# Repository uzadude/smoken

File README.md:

# Smoken!
A temperature controlled fan for charcoal smoker using ESP32.
 
## Background
After taking a welding course, I decided to build a smoker. Shortly after, I realized I must have a solution to keep the temperature steady for many hours. Searching around the internet I found only terribly expensive products (like the [FIREBOARD](https://www.fireboard.com/shop/fireboard-2-drive/?fba_ref=14)). That motivated me to try my first IOT project!

I took this opportunity to gain some skills in the electrical engineering domain.
I used an ESP32 for the MCU (started from [ESP32 starter kit](https://www.ebay.com/itm/303652581313)), built a working prototype using a breadboard and then went on to design a PCB for it (using [KiCad](https://www.kicad.org/)).

I will try to highlight the main lessons learned throughout this process.

## How It Works
- An ESP32 is connected to a thermocouple (with max6675 amplifier) to measure the smoker's current temprature. Another thermocouple is connected just to monitor the meat's temprature.
- The ESP32 is also connected to a 4-pin fan and controls it through a PWM channel with A PID algorithm.
- An external power of 12V/5A is used for both the fan and the ESP32 (through a step-down regulator).
- An 1602 LCD screen is used for simple information.
- A web server is used to monitor the current status, and configure things like the wifi credentials and some paramteres.
- A potentiometer is also available to have manual control over the fan.

### Circuit Schema

### Inventory List

|name|price|quantity|
|----|----|---|
|Esp 32|4|1
|12v power supply|3.7|1
|12v/3A blower fan 4pin|15.4|1
|12v to 5v step down|4|4
|LCD 1602|2.4|1
|max6675|7.3|2
|thermocouple|5.3|2
|small bread board|4.3|3
|4p connector|2.6|10
|wire 4p|5|5m
|3.3k resistor|1.5|300
|wires|3|120

### Afterthoughts
- I could have used a much weaker fan
- Replace the 1602 LCD with 12864 OLED

### Gotchas
- Fan's tacho required RC filter to get the correct reading
- Pin 4 as ADC with wifi.h [bug](https://github.com/espressif/arduino-esp32/issues/102)

## Code
- Use Platform IO as it is way more convenient than the Arduino IDE
- Web server using ESPAsyncWebServer
- Web-based config using AsyncWebConfig
- Use the SPIFFS to save data like a webpage, config file, and data history
- Use git from the beginning

### Gotchas
- [PWM's max freq/precision](src/fan.cpp#L18)

### Some Refs
- basic ESP32 examples:
  - https://lastminuteengineers.com/handling-esp32-gpio-interrupts-tutorial/

- connect max6675:
  - https://github.com/adafruit/MAX6675-library/blob/master/examples/serialthermocouple/serialthermocouple.ino
  - http://www.esp32learning.com/code/esp32-and-max6675-example.php

- connect multiple max6675:
  - https://arduino.stackexchange.com/questions/37193/multiple-3-wire-spi-sensor-interfacing-with-arduino
  - https://forum.arduino.cc/t/problem-with-multiple-max6675-thermocouple/573336/7

- Circuit example:
  - https://github.com/KlausMu/esp32-fan-controller

- PID:
  - https://playground.arduino.cc/Code/PIDLibrary/

- Another ref project:
  - https://github.com/chris948/esp_grillcon/blob/master/esp_grillcon.ino

- Fan specs:
  - https://www.mouser.co.il/datasheet/2/632/BFB1012EH-C18J-1602075.pdf

## PCB

- Used KiCAD
- YouTube tutorial:
  - https://www.youtube.com/watch?v=vaCVh2SAZY4
- Nice getting started tutorial:
  - https://medium.com/invent-io/getting-started-with-embedded-systems-3-schematic-pcb-design-manufacturing-5566b2cf6963
- To search and download additional CAD modules:
  - https://www.snapeda.com/home/
  - https://grabcad.com/library
- Ordered PCB from:
  - https://jlcpcb.com/

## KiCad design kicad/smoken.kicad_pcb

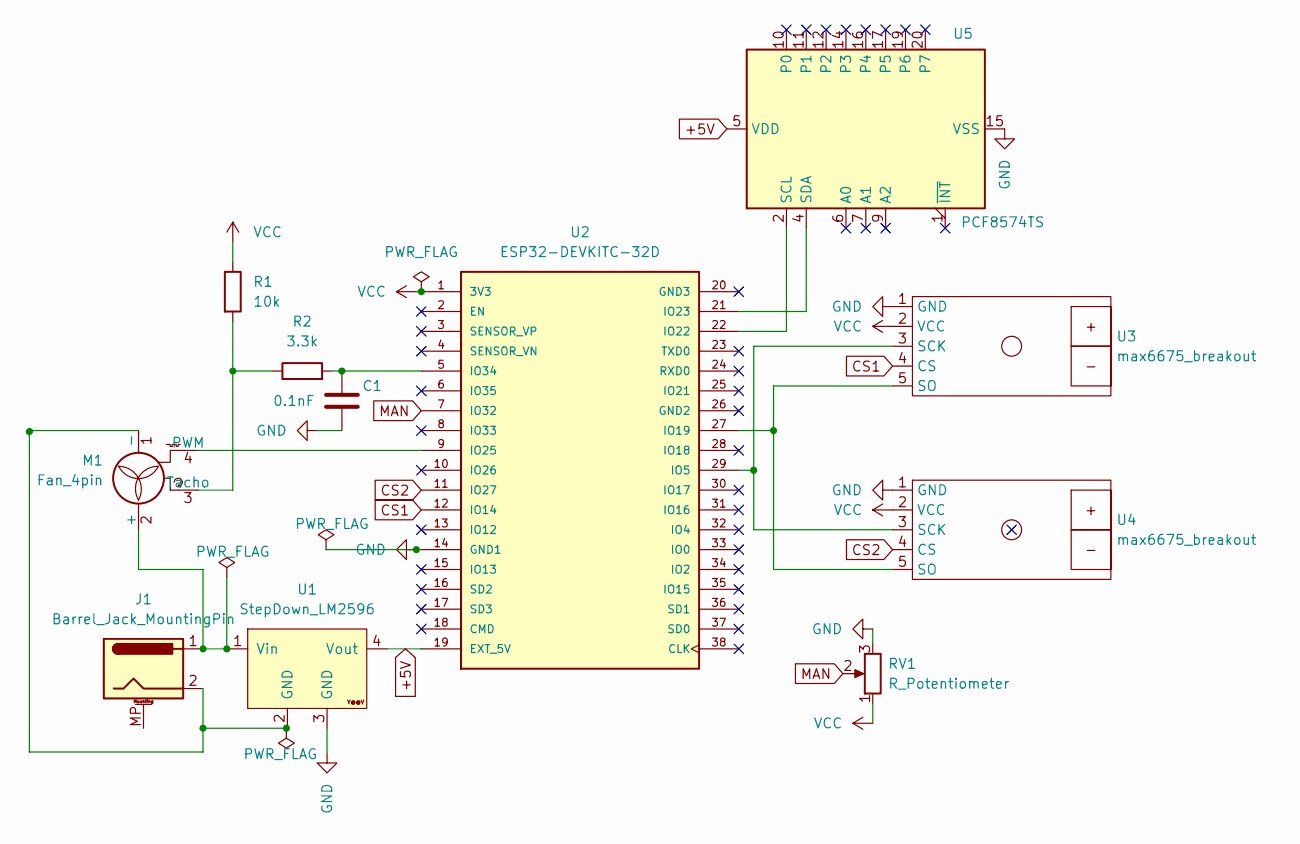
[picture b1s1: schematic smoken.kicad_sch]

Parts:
C1: 0.1nF; CP_Radial_D4.0mm_P2.00mm
J1: Barrel_Jack_MountingPin; BarrelJack_GCT_DCJ200-10-A_Horizontal
M1: Fan_4pin; PinHeader_1x04_P2.54mm_Vertical
R1: 10k; R_Axial_DIN0204_L3.6mm_D1.6mm_P5.08mm_Horizontal
R2: 3.3k; R_Axial_DIN0204_L3.6mm_D1.6mm_P5.08mm_Horizontal
RV1: R_Potentiometer; Potentiometer_Omeg_PC16BU_Vertical
U1: StepDown_LM2596; YAAJ_DCDC_StepDown_LM2596
U2: ESP32-DEVKITC-32D; MODULE_ESP32-DEVKITC-32D; PARTREV 4
U3, U4: max6675_breakout
U5: PCF8574TS; lcd1602_breakout

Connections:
+5V: U1.4 (Vout), U2.19 (EXT_5V), U5.5 (VDD)
CS1: U2.12 (IO14), U3.4 (CS)
CS2: U2.11 (IO27), U4.4 (CS)
GND: C1.2, RV1.3, U1.3 (GND), U2.14 (GND1), U3.1 (GND), U4.1 (GND), U5.15 (VSS)
MAN: RV1.2, U2.7 (IO32)
unnamed: J1.2, M1.1 (-), U1.2 (GND)
unnamed: J1.1, M1.2 (+), U1.1 (Vin)
unnamed: M1.3 (Tacho), R1.2, R2.1
unnamed: C1.1, R2.2, U2.5 (IO34)
unnamed: M1.4 (PWM), U2.9 (IO25)
unnamed: U2.21 (IO23), U5.4 (SDA)
unnamed: U2.22 (IO22), U5.2 (SCL)
unnamed: U2.27 (IO19), U3.5 (SO), U4.5 (SO)
unnamed: U2.29 (IO5), U3.3 (SCK), U4.3 (SCK)
VCC: R1.1, RV1.1, U2.1 (3V3), U3.2 (VCC), U4.2 (VCC)

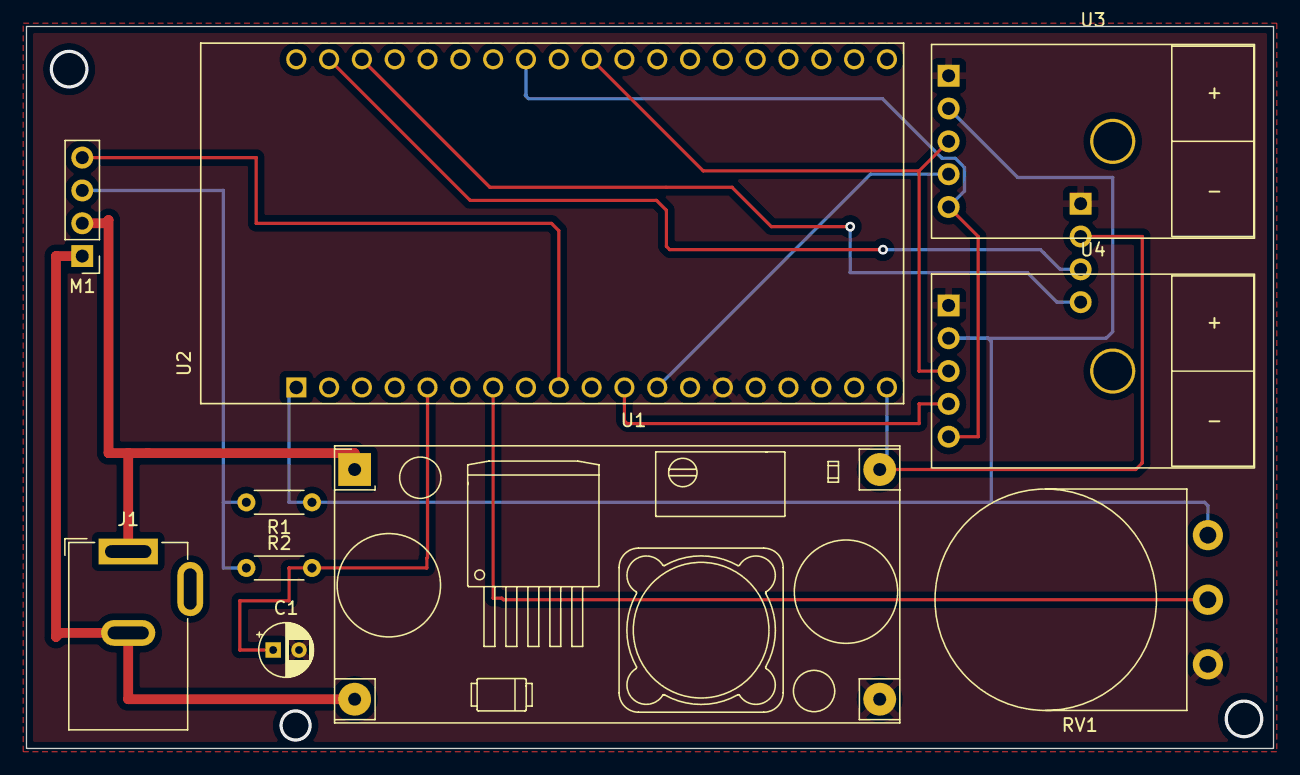
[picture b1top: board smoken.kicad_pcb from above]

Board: 2 copper layers, 96.5 x 55.9 mm, 11 parts (1 on the bottom side), 15 nets.

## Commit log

2021-12-09 working potentiometer with PWM
2021-12-09 added Tacho and fixed PWM wrong precision
2021-12-09 prepare for multi screens
2021-12-09 added one max6675
2021-12-09 adding PID
2021-12-10 Adding readme
2021-12-10 manual override
2021-12-12 adding local wifi
2021-12-12 fixing ADC and wifi bug
2021-12-16 adding second thermocouple
2021-12-16 moving to PIO
2021-12-16 re-factored to separate files
2021-12-16 extracting also PWM
2021-12-18 adding web config
2021-12-19 add web graphics
2021-12-19 Setting AP if can't connect to WiFi
2021-12-19 Inventory List
2021-12-24 sampling the updates
2022-03-15 change thermo CS pin
2022-03-18 PCB - kicad files
2022-03-22 changing PID params from int to float
2022-03-22 serve web page from SPIFFS
2022-03-22 more verbose WiFi connection
2022-03-22 setting PWM to zero on start to prevent fan from start spinning
2022-03-22 down-sampling data and added TS to graphs
2022-03-22 small fixes
2022-03-22 migrating to ESPAsyncWebServer
2022-03-24 wifi reconnection issue
2022-03-27 again updated README
2022-04-07 moving to bootstrap
